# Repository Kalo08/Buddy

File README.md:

https://cdn.hackclub.com/019f5949-5b2a-72fb-9610-620997140d42/BuddyLogo.png

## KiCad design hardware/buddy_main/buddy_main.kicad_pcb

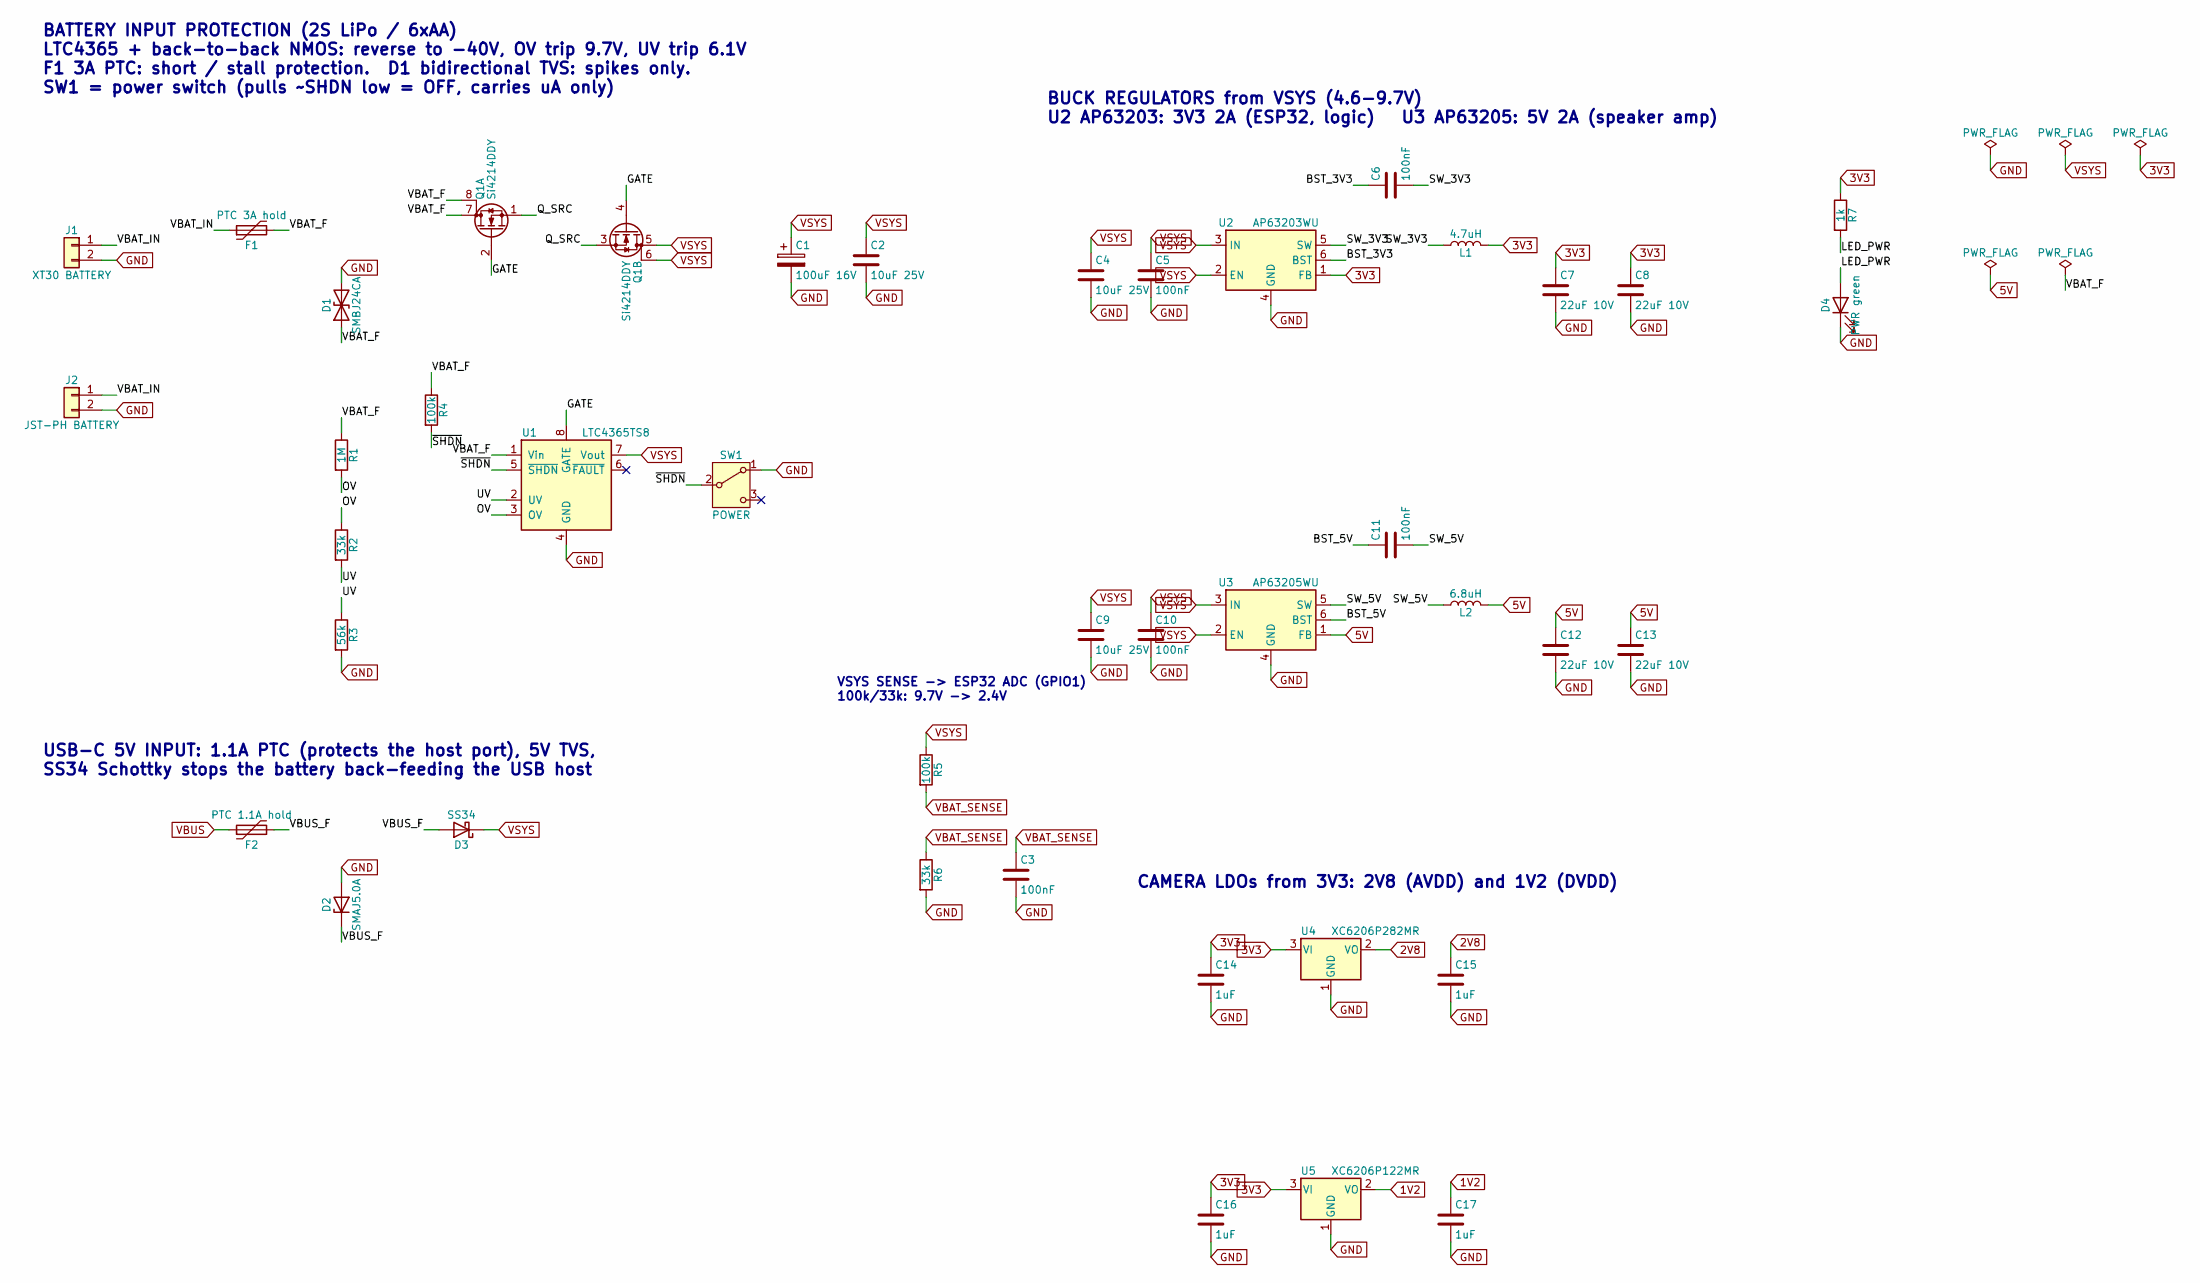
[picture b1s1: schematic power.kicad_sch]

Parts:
C1: 100uF 16V; CP_Elec_6.3x7.7
C2, C4, C9: 10uF 25V; C_1206_3216Metric
C3, C5, C6, C10, C11: 100nF; C_0603_1608Metric
C7, C8, C12, C13: 22uF 10V; C_0805_2012Metric
C14, C15, C16, C17: 1uF; C_0603_1608Metric
D1: SMBJ24CA; D_SMB
D2: SMAJ5.0A; D_SMA
D3: SS34; D_SMA
D4: PWR green; LED_0603_1608Metric
F1: PTC 3A hold; Fuse_2920_7451Metric
F2: PTC 1.1A hold; Fuse_1206_3216Metric
J1: XT30 BATTERY; AMASS_XT30U-M_1x02_P5.0mm_Vertical
J2: JST-PH BATTERY; JST_PH_B2B-PH-K_1x02_P2.00mm_Vertical
L1: 4.7uH; L_Bourns_SRN6045TA
L2: 6.8uH; L_Bourns_SRN6045TA
Q1: Si4214DDY; SOIC-8_3.9x4.9mm_P1.27mm
R1: 1M; R_0603_1608Metric
R2, R6: 33k; R_0603_1608Metric
R3: 56k; R_0603_1608Metric
R4, R5: 100k; R_0603_1608Metric
R7: 1k; R_0603_1608Metric
SW1: POWER; SW_SPDT_PCM12
U1: LTC4365TS8; TSOT-23-8
U2: AP63203WU; TSOT-23-6
U3: AP63205WU; TSOT-23-6
U4: XC6206P282MR; SOT-23-3
U5: XC6206P122MR; SOT-23-3

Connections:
1V2: C17.1, U5.2 (VO); also elsewhere on the board
2V8: C15.1, U4.2 (VO); also elsewhere on the board
3V3: C7.1, C8.1, C14.1, C16.1, L1.2, R7.1, U2.1 (FB), U4.3 (VI), U5.3 (VI); also elsewhere on the board
5V: C12.1, C13.1, L2.2, U3.1 (FB); also elsewhere on the board
/Power and Protection/BST_3V3: C6.1, U2.6 (BST)
/Power and Protection/BST_5V: C11.1, U3.6 (BST)
/Power and Protection/GATE: Q1.2 (G), Q1.4 (G), U1.8 (GATE)
/Power and Protection/LED_PWR: D4.2 (A), R7.2
/Power and Protection/OV: R1.2, R2.1, U1.3 (OV)
/Power and Protection/Q_SRC: Q1.1 (S), Q1.3 (S)
/Power and Protection/SW_3V3: C6.2, L1.1, U2.5 (SW)
/Power and Protection/SW_5V: C11.2, L2.1, U3.5 (SW)
/Power and Protection/UV: R2.2, R3.1, U1.2 (UV)
/Power and Protection/VBAT_F: D1.1 (A1), F1.2, Q1.7 (D), Q1.8 (D), R1.1, R4.1, U1.1 (Vin)
/Power and Protection/VBAT_IN: F1.1, J1.1, J2.1
/Power and Protection/VBUS_F: D2.1 (K), D3.2 (A), F2.2
/Power and Protection/~SHDN: R4.2, SW1.2 (B), U1.5 (~SHDN)
GND: C1.2, C2.2, C3.2, C4.2, C5.2, C7.2, C8.2, C9.2, C10.2, C12.2, C13.2, C14.2, C15.2, C16.2, C17.2, D1.2 (A2), D2.2 (A), D4.1 (K), J1.2, J2.2, R3.2, R6.2, SW1.1 (A), U1.4 (GND), U2.4 (GND), U3.4 (GND), U4.1 (GND), U5.1 (GND); also elsewhere on the board
VBAT_SENSE: C3.1, R5.2, R6.1; also elsewhere on the board
VBUS: F2.1; also elsewhere on the board
VSYS: C1.1, C2.1, C4.1, C5.1, C9.1, C10.1, D3.1 (K), Q1.5 (D), Q1.6 (D), R5.1, U1.7 (Vout), U2.2 (EN), U2.3 (IN), U3.2 (EN), U3.3 (IN); also elsewhere on the board

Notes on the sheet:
BATTERY INPUT PROTECTION (2S LiPo / 6xAA) LTC4365 + back-to-back NMOS: reverse to -40V, OV trip 9.7V, UV trip 6.1V F1 3A PTC: short / stall protection. D1 bidirectional TVS: spikes only. SW1 = power switch (pulls ~SHDN low = OFF, carries uA only)
USB-C 5V INPUT: 1.1A PTC (protects the host port), 5V TVS, SS34 Schottky stops the battery back-feeding the USB host
BUCK REGULATORS from VSYS (4.6-9.7V) U2 AP63203: 3V3 2A (ESP32, logic) U3 AP63205: 5V 2A (speaker amp)
CAMERA LDOs from 3V3: 2V8 (AVDD) and 1V2 (DVDD)
VSYS SENSE -> ESP32 ADC (GPIO1) 100k/33k: 9.7V -> 2.4V

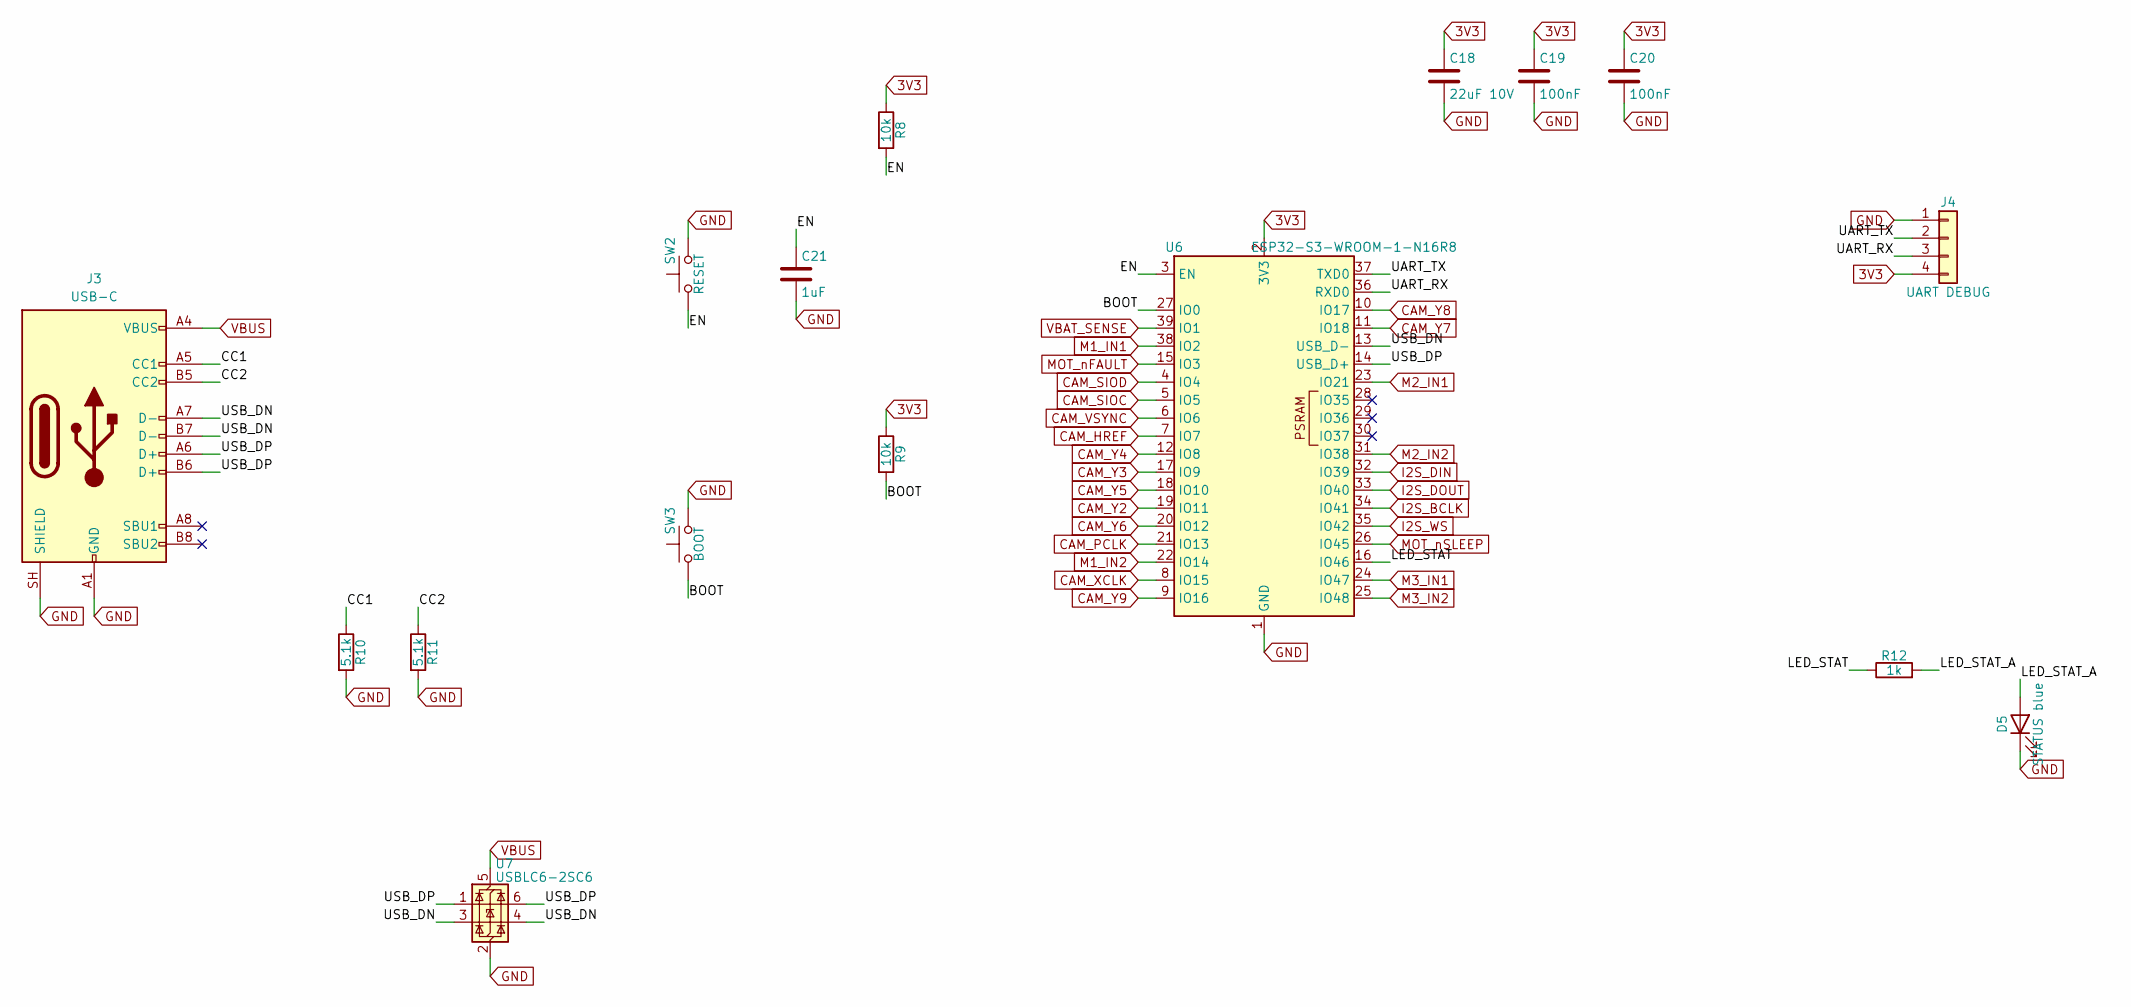
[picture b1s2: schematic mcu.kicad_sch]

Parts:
C18: 22uF 10V; C_0805_2012Metric
C19, C20: 100nF; C_0603_1608Metric
C21: 1uF; C_0603_1608Metric
D5: STATUS blue; LED_0603_1608Metric
J3: USB-C; USB_C_Receptacle_GCT_USB4105-xx-A_16P_TopMnt_Horizontal
J4: UART DEBUG; PinHeader_1x04_P2.54mm_Vertical
R8, R9: 10k; R_0603_1608Metric
R10, R11: 5.1k; R_0603_1608Metric
R12: 1k; R_0603_1608Metric
SW2: RESET; SW_SPST_PTS810
SW3: BOOT; SW_SPST_PTS810
U6: ESP32-S3-WROOM-1-N16R8; ESP32-S3-WROOM-1
U7: USBLC6-2SC6; SOT-23-6

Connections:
3V3: C18.1, C19.1, C20.1, J4.4, R8.1, R9.1, U6.2 (3V3); also elsewhere on the board
/MCU and USB/BOOT: R9.2, SW3.1, U6.27 (IO0)
/MCU and USB/CC1: J3.A5 (CC1), R10.1
/MCU and USB/CC2: J3.B5 (CC2), R11.1
/MCU and USB/EN: C21.1, R8.2, SW2.1, U6.3 (EN)
/MCU and USB/LED_STAT: R12.1, U6.16 (IO46)
/MCU and USB/LED_STAT_A: D5.2 (A), R12.2
/MCU and USB/UART_RX: J4.3, U6.36 (RXD0)
/MCU and USB/UART_TX: J4.2, U6.37 (TXD0)
/MCU and USB/USB_DN: J3.A7 (D-), J3.B7 (D-), U6.13 (USB_D-), U7.3 (I/O2), U7.4 (I/O2)
/MCU and USB/USB_DP: J3.A6 (D+), J3.B6 (D+), U6.14 (USB_D+), U7.1 (I/O1), U7.6 (I/O1)
CAM_HREF: U6.7 (IO7); also elsewhere on the board
CAM_PCLK: U6.21 (IO13); also elsewhere on the board
CAM_SIOC: U6.5 (IO5); also elsewhere on the board
CAM_SIOD: U6.4 (IO4); also elsewhere on the board
CAM_VSYNC: U6.6 (IO6); also elsewhere on the board
CAM_XCLK: U6.8 (IO15); also elsewhere on the board
CAM_Y2: U6.19 (IO11); also elsewhere on the board
CAM_Y3: U6.17 (IO9); also elsewhere on the board
CAM_Y4: U6.12 (IO8); also elsewhere on the board
CAM_Y5: U6.18 (IO10); also elsewhere on the board
CAM_Y6: U6.20 (IO12); also elsewhere on the board
CAM_Y7: U6.11 (IO18); also elsewhere on the board
CAM_Y8: U6.10 (IO17); also elsewhere on the board
CAM_Y9: U6.9 (IO16); also elsewhere on the board
GND: C18.2, C19.2, C20.2, C21.2, D5.1 (K), J3.A1 (GND), J3.A12 (GND), J3.B1 (GND), J3.B12 (GND), J3.SH (SHIELD), J4.1, R10.2, R11.2, SW2.2, SW3.2, U6.1 (GND), U6.40 (GND), U6.41 (GND), U7.2 (GND); also elsewhere on the board
I2S_BCLK: U6.34 (IO41); also elsewhere on the board
I2S_DIN: U6.32 (IO39); also elsewhere on the board
I2S_DOUT: U6.33 (IO40); also elsewhere on the board
I2S_WS: U6.35 (IO42); also elsewhere on the board
M1_IN1: U6.38 (IO2); also elsewhere on the board
M1_IN2: U6.22 (IO14); also elsewhere on the board
M2_IN1: U6.23 (IO21); also elsewhere on the board
M2_IN2: U6.31 (IO38); also elsewhere on the board
M3_IN1: U6.24 (IO47); also elsewhere on the board
M3_IN2: U6.25 (IO48); also elsewhere on the board
MOT_nFAULT: U6.15 (IO3); also elsewhere on the board
MOT_nSLEEP: U6.26 (IO45); also elsewhere on the board
VBAT_SENSE: U6.39 (IO1); also elsewhere on the board
VBUS: J3.A4 (VBUS), J3.A9 (VBUS), J3.B4 (VBUS), J3.B9 (VBUS), U7.5 (VBUS); also elsewhere on the board

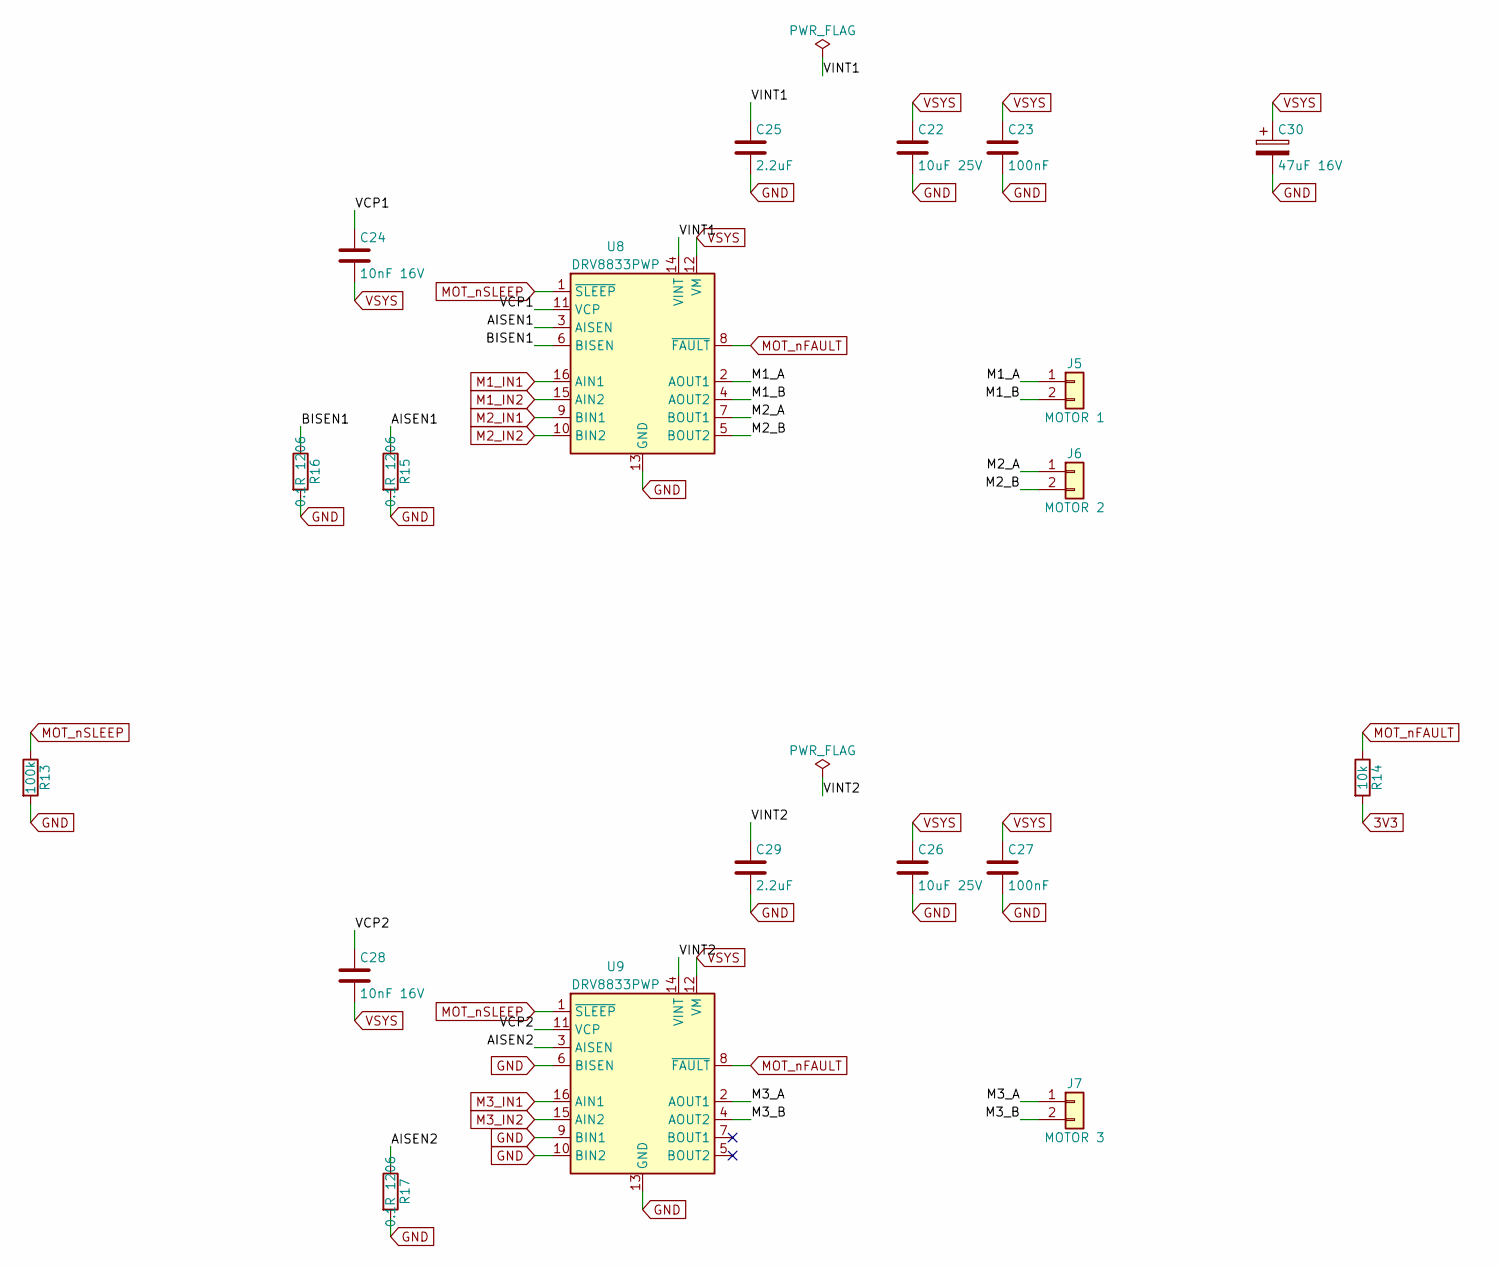
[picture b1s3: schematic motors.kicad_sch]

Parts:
C22, C26: 10uF 25V; C_1206_3216Metric
C23, C27: 100nF; C_0603_1608Metric
C24, C28: 10nF 16V; C_0603_1608Metric
C25, C29: 2.2uF; C_0603_1608Metric
C30: 47uF 16V; CP_Elec_6.3x7.7
J5: MOTOR 1; JST_XH_B2B-XH-A_1x02_P2.50mm_Vertical
J6: MOTOR 2; JST_XH_B2B-XH-A_1x02_P2.50mm_Vertical
J7: MOTOR 3; JST_XH_B2B-XH-A_1x02_P2.50mm_Vertical
R13: 100k; R_0603_1608Metric
R14: 10k; R_0603_1608Metric
R15, R16, R17: 0.1R 1206; R_1206_3216Metric
U8, U9: DRV8833PWP; HTSSOP-16-1EP_4.4x5mm_P0.65mm_EP3.4x5mm_Mask2.46x2.31mm_The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

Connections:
3V3: R14.2; also elsewhere on the board
/Motor Drivers/AISEN1: R15.1, U8.3 (AISEN)
/Motor Drivers/AISEN2: R17.1, U9.3 (AISEN)
/Motor Drivers/BISEN1: R16.1, U8.6 (BISEN)
/Motor Drivers/M1_A: J5.1, U8.2 (AOUT1)
/Motor Drivers/M1_B: J5.2, U8.4 (AOUT2)
/Motor Drivers/M2_A: J6.1, U8.7 (BOUT1)
/Motor Drivers/M2_B: J6.2, U8.5 (BOUT2)
/Motor Drivers/M3_A: J7.1, U9.2 (AOUT1)
/Motor Drivers/M3_B: J7.2, U9.4 (AOUT2)
/Motor Drivers/VCP1: C24.1, U8.11 (VCP)
/Motor Drivers/VCP2: C28.1, U9.11 (VCP)
/Motor Drivers/VINT1: C25.1, U8.14 (VINT)
/Motor Drivers/VINT2: C29.1, U9.14 (VINT)
GND: C22.2, C23.2, C25.2, C26.2, C27.2, C29.2, C30.2, R13.2, R15.2, R16.2, R17.2, U8.13 (GND), U8.17 (GND), U9.6 (BISEN), U9.9 (BIN1), U9.10 (BIN2), U9.13 (GND), U9.17 (GND); also elsewhere on the board
M1_IN1: U8.16 (AIN1); also elsewhere on the board
M1_IN2: U8.15 (AIN2); also elsewhere on the board
M2_IN1: U8.9 (BIN1); also elsewhere on the board
M2_IN2: U8.10 (BIN2); also elsewhere on the board
M3_IN1: U9.16 (AIN1); also elsewhere on the board
M3_IN2: U9.15 (AIN2); also elsewhere on the board
MOT_nFAULT: R14.1, U8.8 (~FAULT), U9.8 (~FAULT); also elsewhere on the board
MOT_nSLEEP: R13.1, U8.1 (~SLEEP), U9.1 (~SLEEP); also elsewhere on the board
VSYS: C22.1, C23.1, C24.2, C26.1, C27.1, C28.2, C30.1, U8.12 (VM), U9.12 (VM); also elsewhere on the board

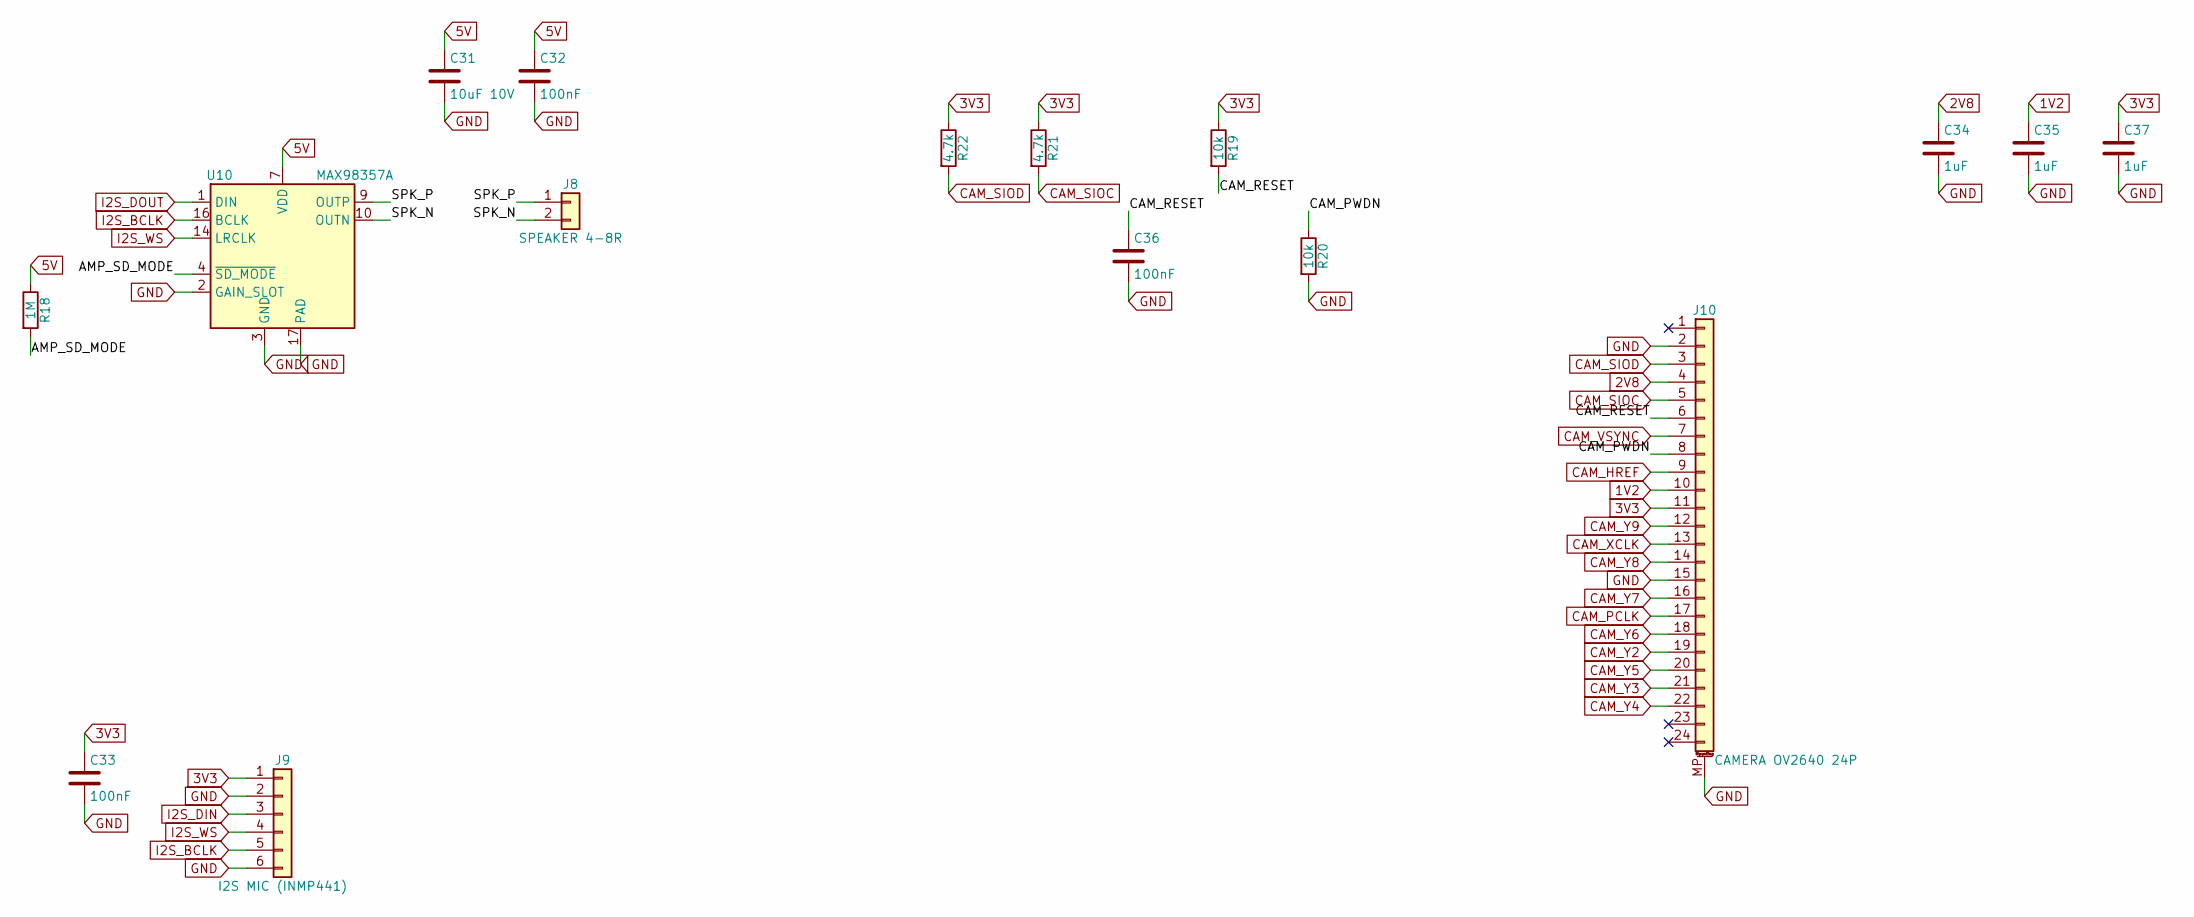
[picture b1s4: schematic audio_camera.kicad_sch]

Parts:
C31: 10uF 10V; C_0805_2012Metric
C32, C33, C36: 100nF; C_0603_1608Metric
C34, C35, C37: 1uF; C_0603_1608Metric
J8: SPEAKER 4-8R; JST_PH_B2B-PH-K_1x02_P2.00mm_Vertical
J9: I2S MIC (INMP441); PinSocket_1x06_P2.54mm_Vertical
J10: CAMERA OV2640 24P; Hirose_FH12-24S-0.5SH_1x24-1MP_P0.50mm_Horizontal
R18: 1M; R_0603_1608Metric
R19, R20: 10k; R_0603_1608Metric
R21, R22: 4.7k; R_0603_1608Metric
U10: MAX98357A; TQFN-16-1EP_3x3mm_P0.5mm_EP1.23x1.23mm

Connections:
1V2: C35.1, J10.10; also elsewhere on the board
2V8: C34.1, J10.4; also elsewhere on the board
3V3: C33.1, C37.1, J9.1, J10.11, R19.1, R21.1, R22.1; also elsewhere on the board
5V: C31.1, C32.1, R18.1, U10.7 (VDD), U10.8 (VDD); also elsewhere on the board
/Audio and Camera/AMP_SD_MODE: R18.2, U10.4 (~SD_MODE)
/Audio and Camera/CAM_PWDN: J10.8, R20.1
/Audio and Camera/CAM_RESET: C36.1, J10.6, R19.2
/Audio and Camera/SPK_N: J8.2, U10.10 (OUTN)
/Audio and Camera/SPK_P: J8.1, U10.9 (OUTP)
CAM_HREF: J10.9; also elsewhere on the board
CAM_PCLK: J10.17; also elsewhere on the board
CAM_SIOC: J10.5, R21.2; also elsewhere on the board
CAM_SIOD: J10.3, R22.2; also elsewhere on the board
CAM_VSYNC: J10.7; also elsewhere on the board
CAM_XCLK: J10.13; also elsewhere on the board
CAM_Y2: J10.19; also elsewhere on the board
CAM_Y3: J10.21; also elsewhere on the board
CAM_Y4: J10.22; also elsewhere on the board
CAM_Y5: J10.20; also elsewhere on the board
CAM_Y6: J10.18; also elsewhere on the board
CAM_Y7: J10.16; also elsewhere on the board
CAM_Y8: J10.14; also elsewhere on the board
CAM_Y9: J10.12; also elsewhere on the board
GND: C31.2, C32.2, C33.2, C34.2, C35.2, C36.2, C37.2, J9.2, J9.6, J10.2, J10.15, J10.MP (MountPin), R20.2, U10.2 (GAIN_SLOT), U10.3 (GND), U10.11 (GND), U10.15 (GND), U10.17 (PAD); also elsewhere on the board
I2S_BCLK: J9.5, U10.16 (BCLK); also elsewhere on the board
I2S_DIN: J9.3; also elsewhere on the board
I2S_DOUT: U10.1 (DIN); also elsewhere on the board
I2S_WS: J9.4, U10.14 (LRCLK); also elsewhere on the board

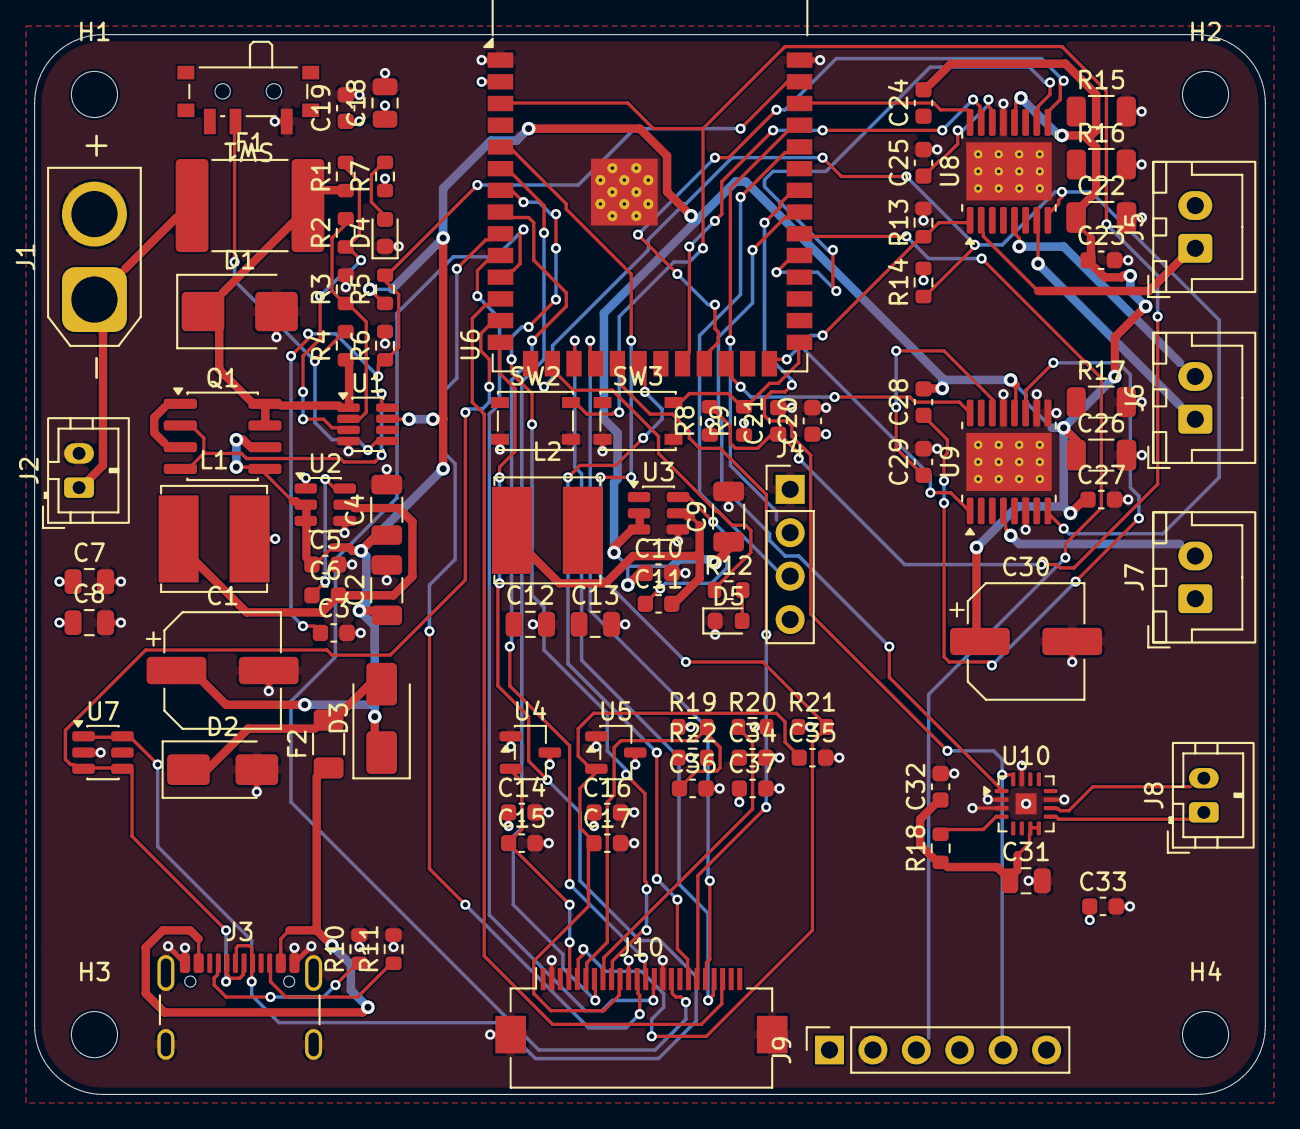
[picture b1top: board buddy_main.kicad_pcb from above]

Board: 4 copper layers, 72.0 x 62.0 mm, 96 parts (0 on the bottom side), 75 nets.

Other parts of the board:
H1, H2, H3, H4: MountingHole_2.7mm

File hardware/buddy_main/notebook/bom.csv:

"Refs","Value","Footprint","Qty"
"C1","100uF 16V","Capacitor_SMD:CP_Elec_6.3x7.7","1"
"C2,C4,C9,C22,C26","10uF 25V","Capacitor_SMD:C_1206_3216Metric","5"
"C3,C5,C6,C10,C11,C19,C20,C23,C27,C32,C33,C36","100nF","Capacitor_SMD:C_0603_1608Metric","12"
"C7,C8,C12,C13,C18","22uF 10V","Capacitor_SMD:C_0805_2012Metric","5"
"C14-C17,C21,C34,C35,C37","1uF","Capacitor_SMD:C_0603_1608Metric","8"
"C24,C28","10nF 16V","Capacitor_SMD:C_0603_1608Metric","2"
"C25,C29","2.2uF","Capacitor_SMD:C_0603_1608Metric","2"
"C30","47uF 16V","Capacitor_SMD:CP_Elec_6.3x7.7","1"
"C31","10uF 10V","Capacitor_SMD:C_0805_2012Metric","1"
"D1","SMBJ24CA","Diode_SMD:D_SMB","1"
"D2","SMAJ5.0A","Diode_SMD:D_SMA","1"
"D3","SS34","Diode_SMD:D_SMA","1"
"D4","PWR green","LED_SMD:LED_0603_1608Metric","1"
"D5","STATUS blue","LED_SMD:LED_0603_1608Metric","1"
"F1","PTC 3A hold","Fuse:Fuse_2920_7451Metric","1"
"F2","PTC 1.1A hold","Fuse:Fuse_1206_3216Metric","1"
"J1","XT30 BATTERY","Connector_AMASS:AMASS_XT30U-M_1x02_P5.0mm_Vertical","1"
"J2","JST-PH BATTERY","Connector_JST:JST_PH_B2B-PH-K_1x02_P2.00mm_Vertical","1"
"J3","USB-C","Connector_USB:USB_C_Receptacle_GCT_USB4105-xx-A_16P_TopMnt_Horizontal","1"
"J4","UART DEBUG","Connector_PinHeader_2.54mm:PinHeader_1x04_P2.54mm_Vertical","1"
"J5","MOTOR 1","Connector_JST:JST_XH_B2B-XH-A_1x02_P2.50mm_Vertical","1"
"J6","MOTOR 2","Connector_JST:JST_XH_B2B-XH-A_1x02_P2.50mm_Vertical","1"
"J7","MOTOR 3","Connector_JST:JST_XH_B2B-XH-A_1x02_P2.50mm_Vertical","1"
"J8","SPEAKER 4-8R","Connector_JST:JST_PH_B2B-PH-K_1x02_P2.00mm_Vertical","1"
"J9","I2S MIC (INMP441)","Connector_PinSocket_2.54mm:PinSocket_1x06_P2.54mm_Vertical","1"
"J10","CAMERA OV2640 24P","Connector_FFC-FPC:Hirose_FH12-24S-0.5SH_1x24-1MP_P0.50mm_Horizontal","1"
"L1","4.7uH","Inductor_SMD:L_Bourns_SRN6045TA","1"
"L2","6.8uH","Inductor_SMD:L_Bourns_SRN6045TA","1"
"Q1","Si4214DDY","Package_SO:SOIC-8_3.9x4.9mm_P1.27mm","1"
"R1,R18","1M","Resistor_SMD:R_0603_1608Metric","2"
"R2,R6","33k","Resistor_SMD:R_0603_1608Metric","2"
"R3","56k","Resistor_SMD:R_0603_1608Metric","1"
"R4,R5,R13","100k","Resistor_SMD:R_0603_1608Metric","3"
"R7,R12","1k","Resistor_SMD:R_0603_1608Metric","2"
"R8,R9,R14,R19,R20","10k","Resistor_SMD:R_0603_1608Metric","5"
"R10,R11","5.1k","Resistor_SMD:R_0603_1608Metric","2"
"R15-R17","0.1R 1206","Resistor_SMD:R_1206_3216Metric","3"
"R21,R22","4.7k","Resistor_SMD:R_0603_1608Metric","2"
"SW1","POWER","Button_Switch_SMD:SW_SPDT_PCM12","1"
"SW2","RESET","Button_Switch_SMD:SW_SPST_PTS810","1"
"SW3","BOOT","Button_Switch_SMD:SW_SPST_PTS810","1"
"U1","LTC4365TS8","Package_TO_SOT_SMD:TSOT-23-8","1"
"U2","AP63203WU","Package_TO_SOT_SMD:TSOT-23-6","1"
"U3","AP63205WU","Package_TO_SOT_SMD:TSOT-23-6","1"
"U4","XC6206P282MR","Package_TO_SOT_SMD:SOT-23-3","1"
"U5","XC6206P122MR","Package_TO_SOT_SMD:SOT-23-3","1"
"U6","ESP32-S3-WROOM-1-N16R8","RF_Module:ESP32-S3-WROOM-1","1"
"U7","USBLC6-2SC6","Package_TO_SOT_SMD:SOT-23-6","1"
"U8,U9","DRV8833PWP","Package_SO:HTSSOP-16-1EP_4.4x5mm_P0.65mm_EP3.4x5mm_Mask2.46x2.31mm_ThermalVias","2"
"U10","MAX98357A","Package_DFN_QFN:TQFN-16-1EP_3x3mm_P0.5mm_EP1.23x1.23mm","1"

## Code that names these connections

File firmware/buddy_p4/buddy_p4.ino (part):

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#define I2C_SDA        7    // shared: ES8311 + camera SCCB
#define I2C_SCL        8
#define I2S_MCLK      13
#define I2S_BCLK      12
#define I2S_WS        10
#define I2S_DOUT       9    // → ES8311 DSDIN
#define I2S_DIN       11    // ← ES8311 ASDOUT (onboard mic)
#define SPK_PA_EN     53    // speaker amp enable

#define SERVO_PIN_FL  20
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  std.slot_cfg = I2S_STD_PHILIPS_SLOT_DEFAULT_CONFIG(I2S_DATA_BIT_WIDTH_16BIT, I2S_SLOT_MODE_MONO);
  std.slot_cfg.slot_mask = I2S_STD_SLOT_BOTH;  // same audio on both slots, whichever the DAC uses
  std.gpio_cfg.mclk = (gpio_num_t)I2S_MCLK;
  std.gpio_cfg.bclk = (gpio_num_t)I2S_BCLK;
  std.gpio_cfg.ws   = (gpio_num_t)I2S_WS;
  std.gpio_cfg.dout = (gpio_num_t)I2S_DOUT;
  std.gpio_cfg.din  = MIC_ENABLED ? (gpio_num_t)I2S_DIN : I2S_GPIO_UNUSED;
  if (i2s_channel_init_std_mode(i2sTx, &std) != ESP_OK || i2s_channel_enable(i2sTx) != ESP_OK) {
    Serial.println("[spk] init FAILED — I2S config"); return;
  }
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
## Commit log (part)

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2026-06-22 boom
2026-06-22 Bleh
